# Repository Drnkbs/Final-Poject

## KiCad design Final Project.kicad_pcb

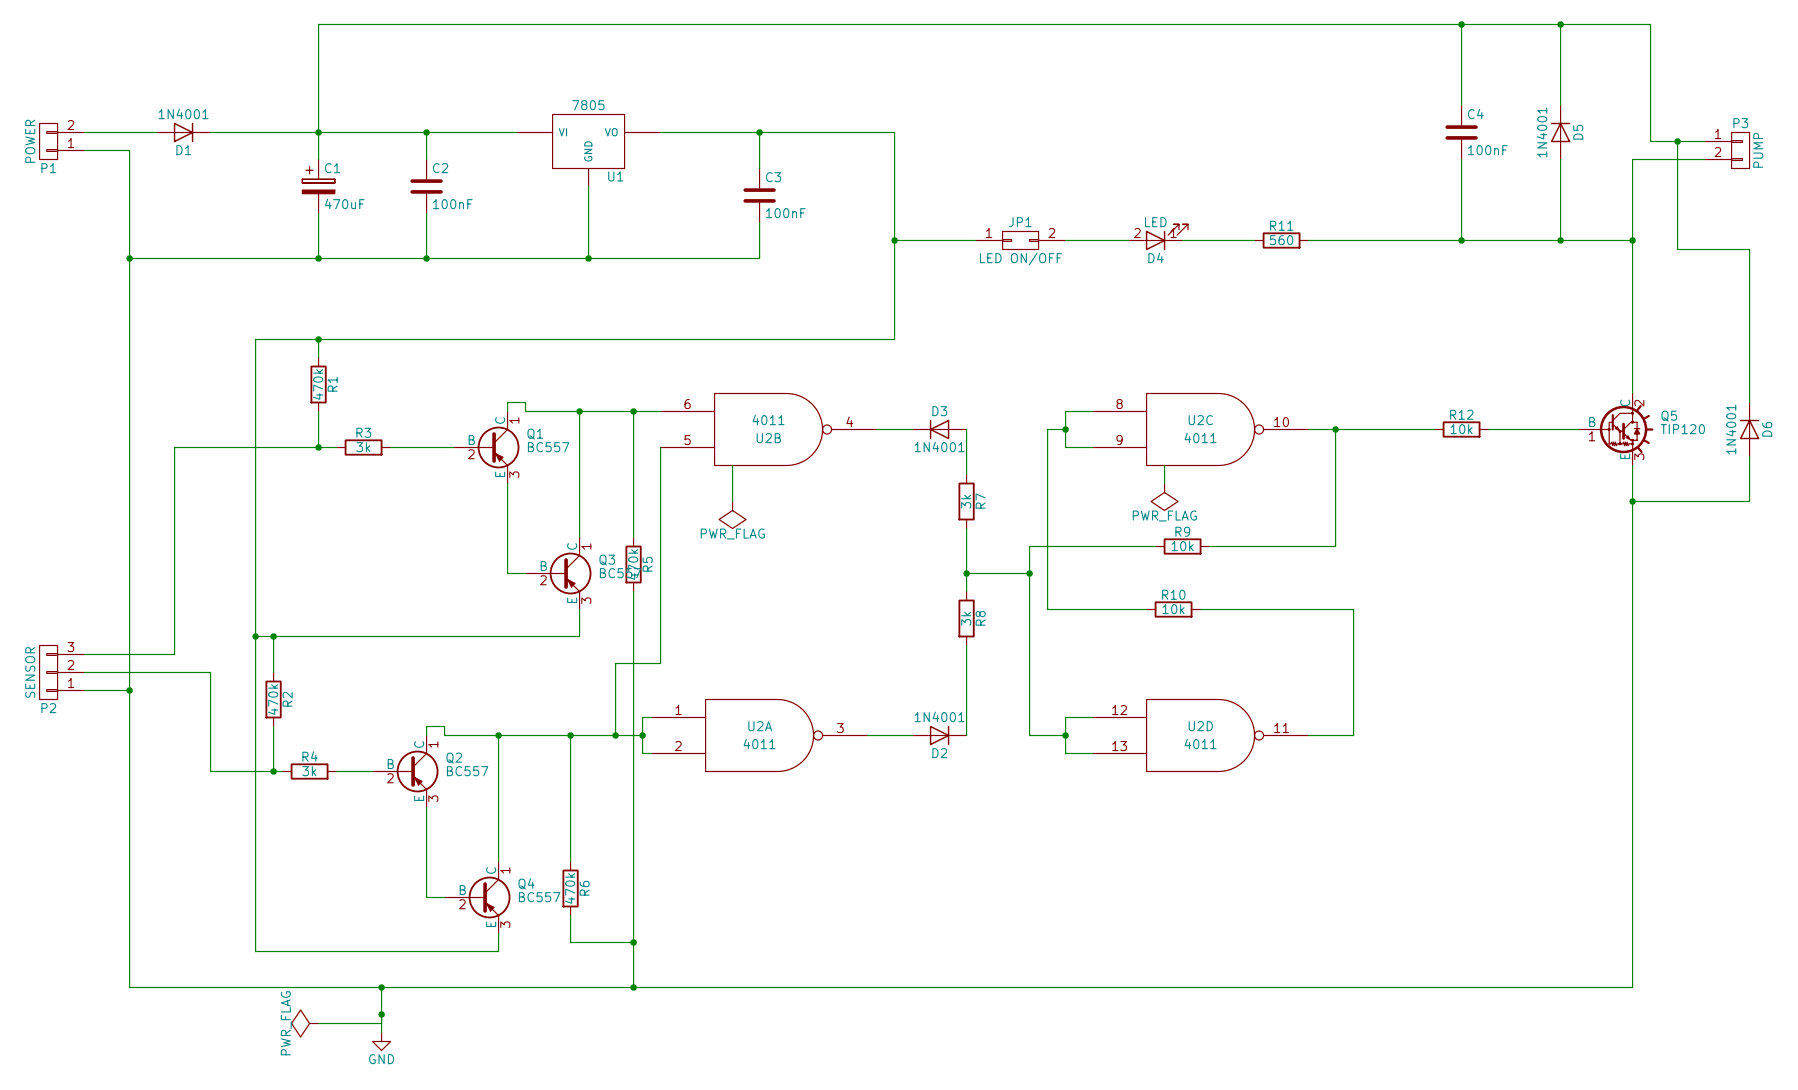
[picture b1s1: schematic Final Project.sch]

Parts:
C1: 470uF; CP_Radial_Tantal_D8.0mm_P2.50mm
C2, C3, C4: 100nF; CP_Axial_L11.0mm_D5.0mm_P18.00mm_Horizontal
D1, D2, D3, D5, D6: 1N4001; D_A-405_P10.16mm_Horizontal
D4: LED; LED_D8.0mm
JP1: LED ON/OFF; JP-X
P1: POWER; PINHEAD1-2
P2: SENSOR; PINHEAD1-3
P3: PUMP; PINHEAD1-2
Q1, Q2, Q3, Q4: BC557; TO-92_Molded_Narrow
Q5: TIP120; TO-280_Vertical
R1, R2, R5, R6: 470k; R_Axial_DIN0207_L6.3mm_D2.5mm_P10.16mm_Horizontal
R3, R4, R7, R8: 3k; R_Axial_DIN0207_L6.3mm_D2.5mm_P10.16mm_Horizontal
R9, R10, R12: 10k; R_Axial_DIN0207_L6.3mm_D2.5mm_P10.16mm_Horizontal
R11: 560; R_Axial_DIN0207_L6.3mm_D2.5mm_P10.16mm_Horizontal
U1: 7805; 78XXX
U2: 4011; DIP-14_W7.62mm

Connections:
GND: C1.2, C2.2, C3.2, D6.2 (A), P1.1, P2.1, Q5.3 (E), R5.2, R6.2, U1.GND
unnamed: C1.1, C2.1, C4.1, D1.1 (K), D5.1 (K), D6.1 (K), P3.1, U1.VI
unnamed: C3.1, JP1.1, Q3.3 (E), Q4.3 (E), R1.1, R2.1, U1.VO
unnamed: C4.2, D5.2 (A), P3.2, Q5.2 (C), R11.2
unnamed: D1.2 (A), P1.2
unnamed: D2.1 (K), R8.2
unnamed: D2.2 (A), U2.3
unnamed: D3.1 (K), U2.4
unnamed: D3.2 (A), R7.1
unnamed: D4.1 (K), R11.1
unnamed: D4.2 (A), JP1.2
unnamed: P2.2, R2.2, R4.1
unnamed: P2.3, R1.2, R3.1
unnamed: Q1.1 (C), Q3.1 (C), R5.1, U2.6
unnamed: Q1.2 (B), R3.2
unnamed: Q1.3 (E), Q3.2 (B)
unnamed: Q2.1 (C), Q4.1 (C), R6.1, U2.1, U2.2, U2.5
unnamed: Q2.2 (B), R4.2
unnamed: Q2.3 (E), Q4.2 (B)
unnamed: Q5.1 (B), R12.2
unnamed: R7.2, R8.1, R9.1, U2.12, U2.13
unnamed: R10.1, U2.8, U2.9
unnamed: R10.2, U2.11
unnamed: R9.2, R12.1, U2.10
VDD: U2.14 (VDD)
VSS: U2.7 (VSS)

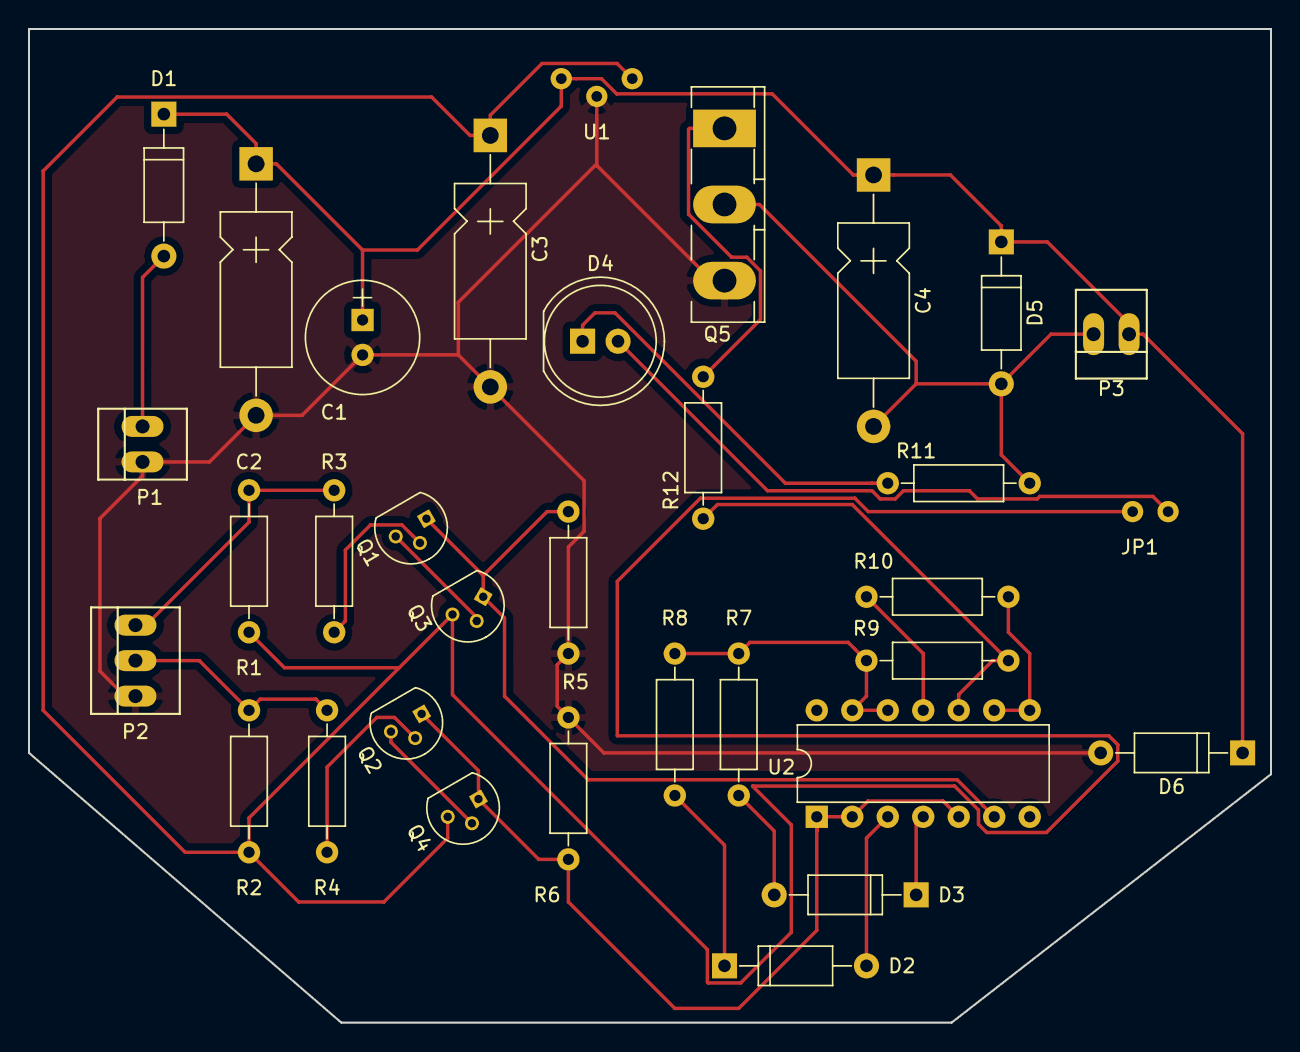
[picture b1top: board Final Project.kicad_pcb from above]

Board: 2 copper layers, 88.9 x 71.1 mm, 33 parts (0 on the bottom side), 24 nets.

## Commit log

2017-06-13 Final project
